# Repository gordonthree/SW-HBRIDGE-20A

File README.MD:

# High / Low Smart Switch Node
* BTS50010 Profet Smart Switch for high side loads
* VNB35N07 OMNIFET Protected MOSFET for low side loads
* Microchip MCP1416 gate driver to ensure maximum low side efficiency
* Heavy duty terminal block connectors for power in/out
* Pin-header connections for linking to a can bus control module
* Low side switch uses VS line, adjust control board accordingly
<IMG src="https://github.com/gordonthree/SW-HBRIDGE-20A/blob/main/SW-HBRIDGE-20A.png?raw=true" width=480>

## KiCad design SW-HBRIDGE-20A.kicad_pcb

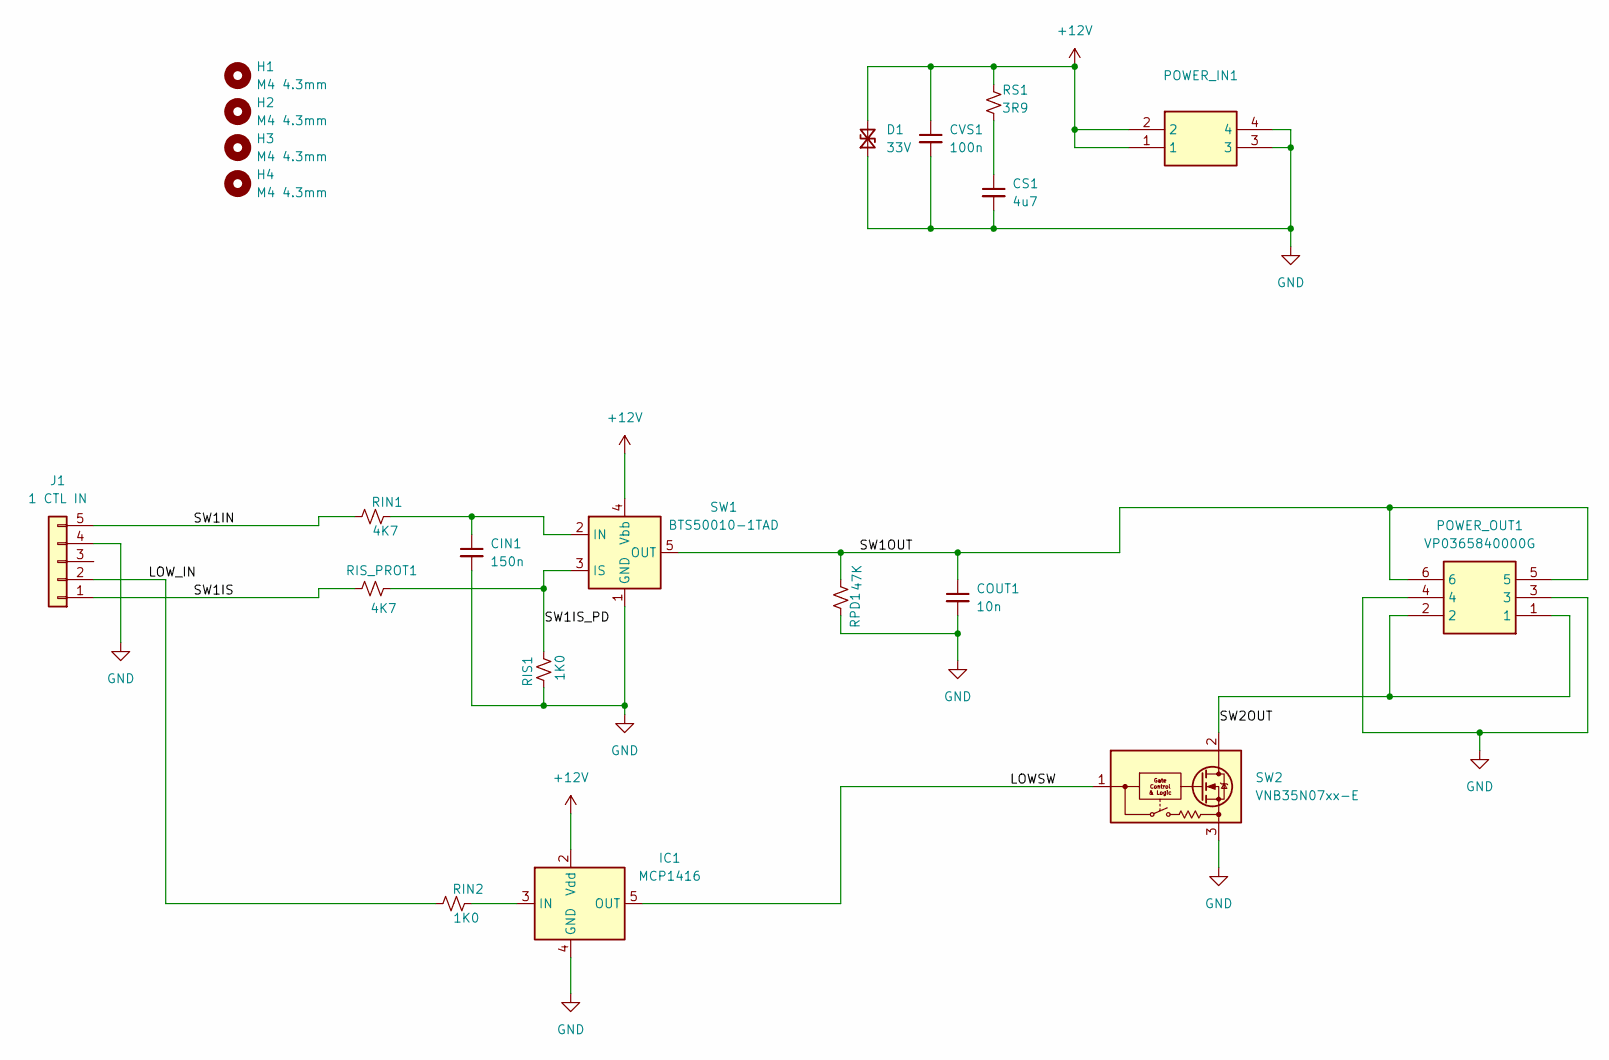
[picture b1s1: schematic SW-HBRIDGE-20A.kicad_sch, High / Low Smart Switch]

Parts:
CIN1: 150n; C_0603_1608Metric_Pad1.08x0.95mm_HandSolder
COUT1: 10n; C_0603_1608Metric_Pad1.08x0.95mm_HandSolder
CS1: 4u7; C_0603_1608Metric_Pad1.08x0.95mm_HandSolder
CVS1: 100n; C_0603_1608Metric_Pad1.08x0.95mm_HandSolder
D1: 33V; D_SMA_Handsoldering
H1, H2, H3, H4: M4 4.3mm; MountingHole_4.3mm_M4
IC1: MCP1416; SOT-23-5
J1: 1 CTL IN; PinHeader_1x05_P2.54mm_Horizontal
POWER_IN1: PWRIN; VP0265840000G; Mouser Part Number 649-VP02658400J0G
POWER_OUT1: VP0365840000G; Mouser Part Number 649-VP03658400J0G
RIN1: 4K7; R_0603_1608Metric_Pad0.98x0.95mm_HandSolder
RIN2: 1K0; R_0603_1608Metric_Pad0.98x0.95mm_HandSolder
RIS1: 1K0; R_0603_1608Metric_Pad0.98x0.95mm_HandSolder
RIS_PROT1: 4K7; R_0603_1608Metric_Pad0.98x0.95mm_HandSolder
RPD1: 47K; R_0603_1608Metric_Pad0.98x0.95mm_HandSolder
RS1: 3R9; R_0603_1608Metric_Pad0.98x0.95mm_HandSolder
SW1: BTS50010-1TAD; TO-263-7_TabPin4
SW2: VNB35N07xx-E; TO-263-2

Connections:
+12V: CVS1.1, D1.2 (A2), IC1.2 (Vdd), POWER_IN1.1, POWER_IN1.2, RS1.2, SW1.4 (Vbb)
/LOWSW: IC1.5 (OUT), SW2.1 (INPUT)
/LOW_IN: J1.2, RIN2.1
/SW1IN: J1.5, RIN1.1
/SW1IS: J1.1, RIS_PROT1.1
/SW1IS_PD: RIS1.2, RIS_PROT1.2, SW1.3 (IS)
/SW1OUT: COUT1.1, POWER_OUT1.5, POWER_OUT1.6, RPD1.2, SW1.5 (OUT), SW1.6 (OUT), SW1.7 (OUT)
/SW2OUT: POWER_OUT1.1, POWER_OUT1.2, SW2.2 (DRAIN)
GND: CIN1.2, COUT1.2, CS1.2, CVS1.2, D1.1 (A1), IC1.4 (GND), J1.4, POWER_IN1.3, POWER_IN1.4, POWER_OUT1.3, POWER_OUT1.4, RIS1.1, RPD1.1, SW1.1 (GND), SW2.3 (SOURCE)
unnamed: CS1.1, RS1.1
unnamed: IC1.3 (IN), RIN2.2
unnamed: CIN1.1, RIN1.2, SW1.2 (IN)

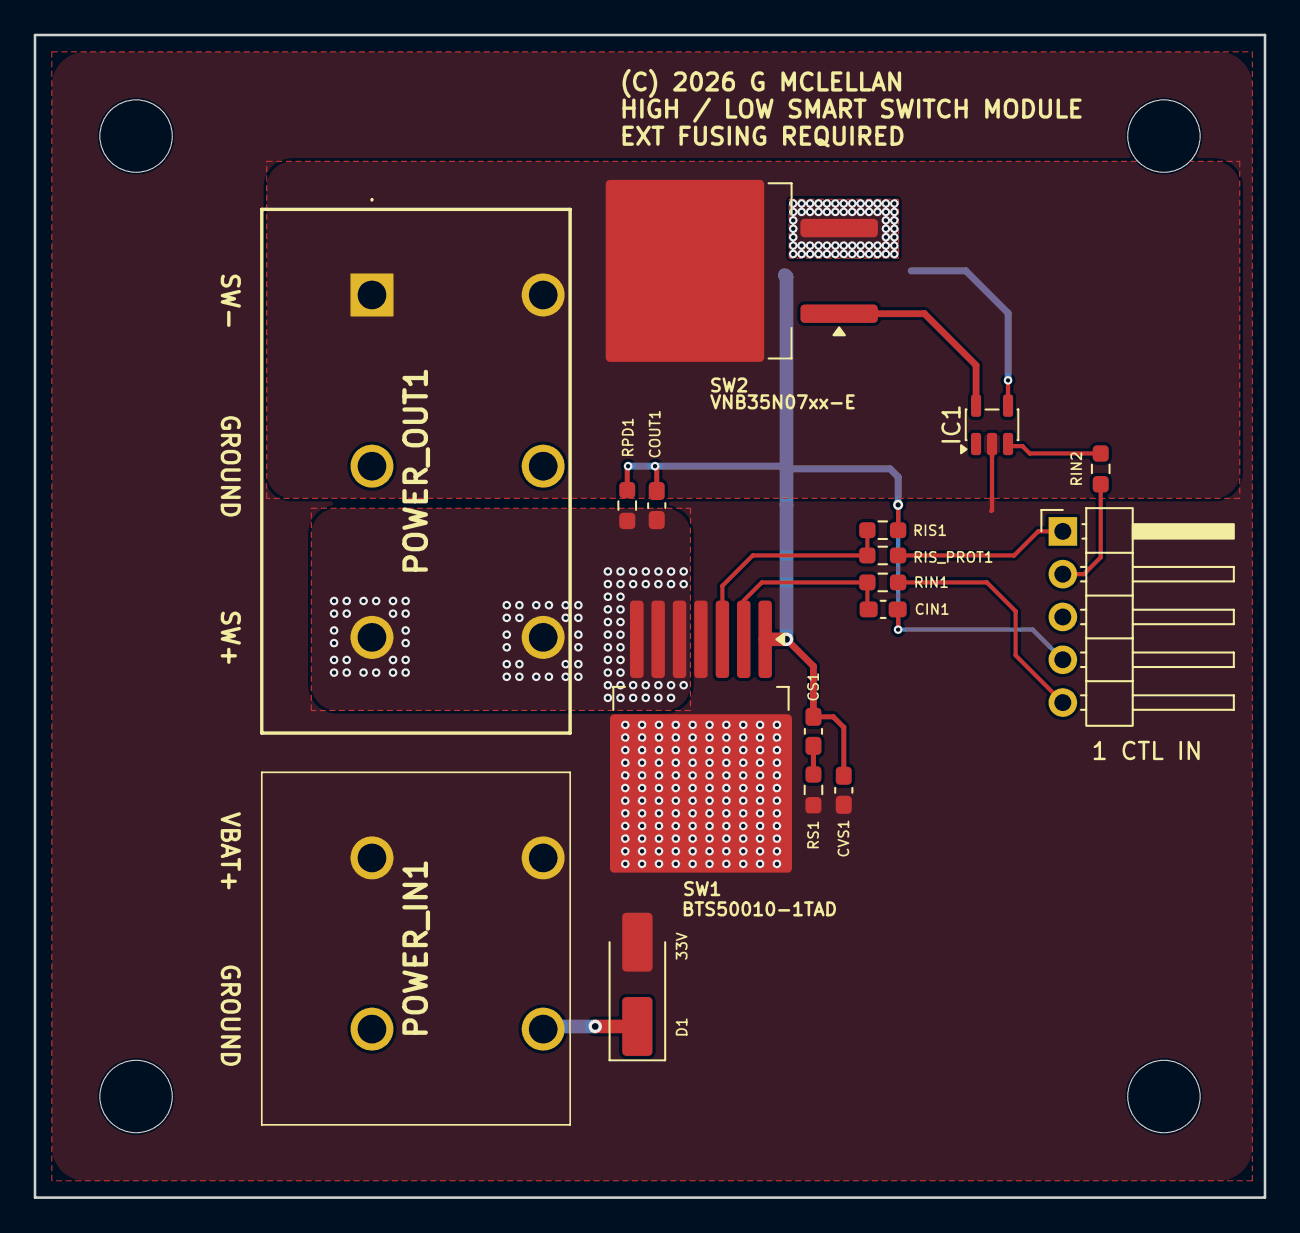
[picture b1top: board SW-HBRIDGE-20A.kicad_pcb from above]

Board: 2 copper layers, 73.0 x 69.0 mm, 21 parts (0 on the bottom side), 12 nets.

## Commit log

2026-01-18 updated embedded image
2026-01-18 updated rendering
2026-01-18 silkscreen tweak

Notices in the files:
SW-HBRIDGE-20A.kicad_pcb:
(C) 2026 G MCLELLAN
